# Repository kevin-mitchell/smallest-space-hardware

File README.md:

# smallest-space-hardware
smallest.space hardware related project files

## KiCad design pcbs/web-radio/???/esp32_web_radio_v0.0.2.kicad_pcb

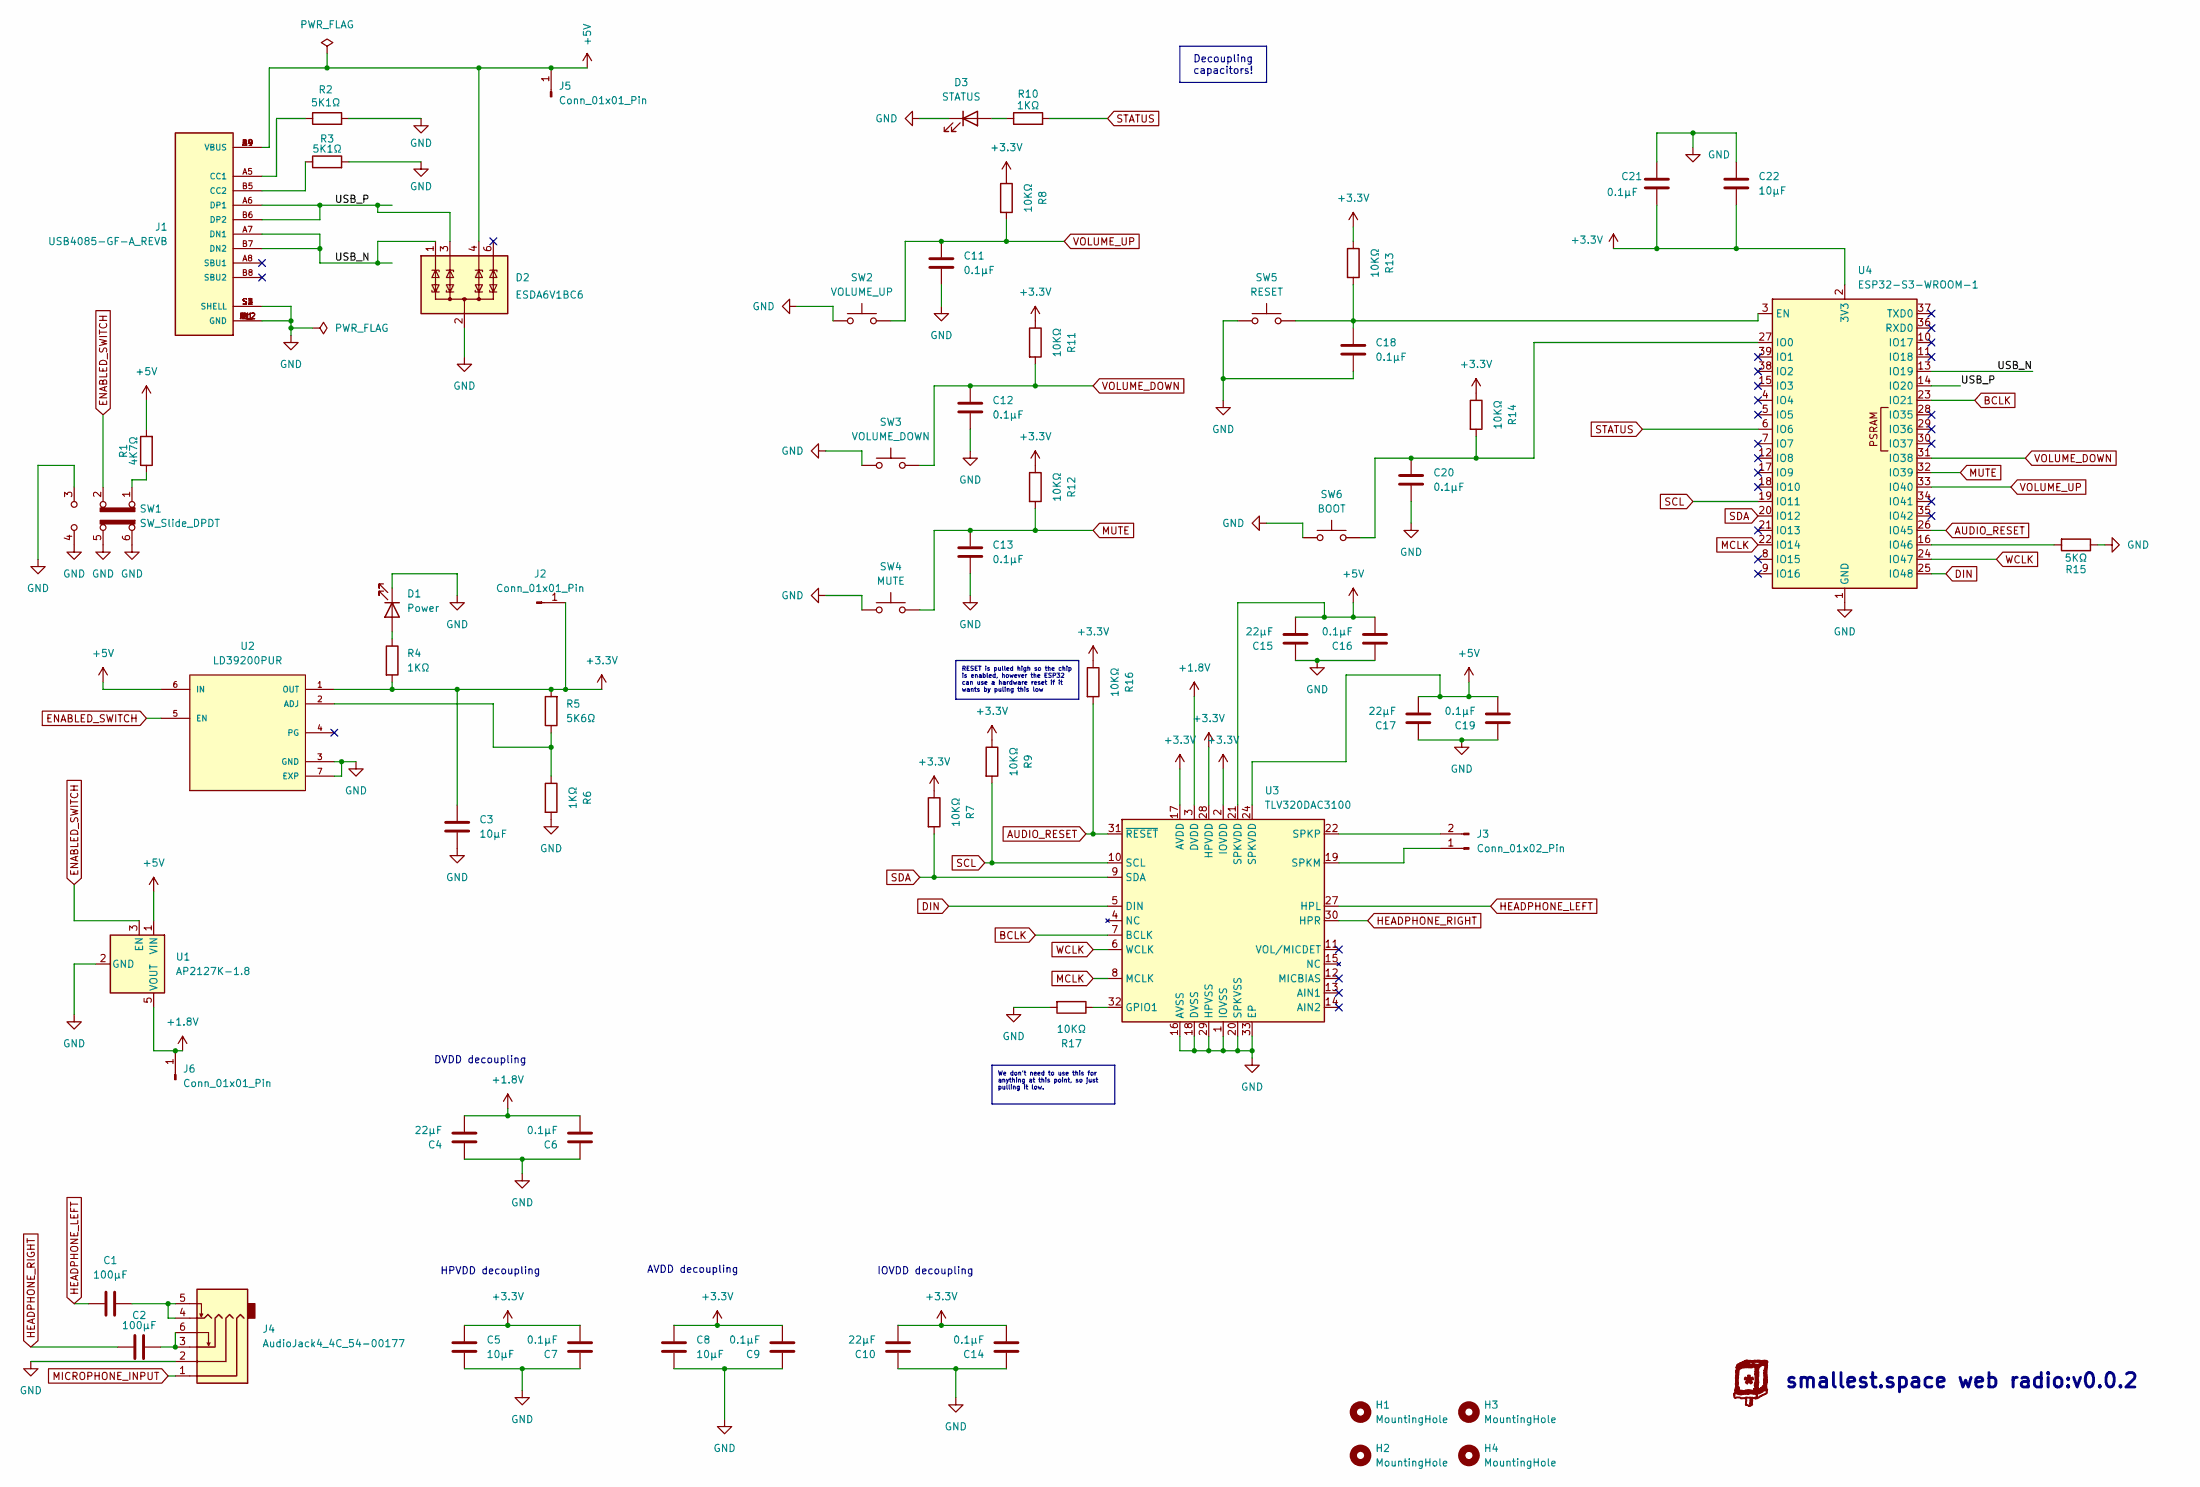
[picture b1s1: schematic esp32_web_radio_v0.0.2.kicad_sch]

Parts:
C1, C2: 100µF; C_1206_3216Metric_Pad1.33x1.80mm_HandSolder
C3, C22: 10µF; C_0805_2012Metric_Pad1.18x1.45mm_HandSolder
C4, C10, C15, C17: 22µF; C_0603_1608Metric_Pad1.08x0.95mm_HandSolder
C5, C8: 10µF; C_0603_1608Metric_Pad1.08x0.95mm_HandSolder
C6, C7, C9, C14, C16, C19: 0.1µF; C_0603_1608Metric_Pad1.08x0.95mm_HandSolder
C11, C12, C13, C18, C20, C21: 0.1µF; C_0805_2012Metric_Pad1.18x1.45mm_HandSolder
D1: Power; LED_0805_2012Metric_Pad1.15x1.40mm_HandSolder
D2: ESDA6V1BC6; SOT-23-6
D3: STATUS; LED_0805_2012Metric_Pad1.15x1.40mm_HandSolder
H1, H2, H3, H4: MountingHole; MountingHole_2.7mm
J1: USB4085-GF-A_REVB; GCT_USB4085-GF-A_REVB; PARTREV B; DigiKey_Part_Number 2073-USB4085-GF-ATR-ND
J2, J5, J6: Conn_01x01_Pin; TestPoint_Pad_1.0x1.0mm
J3: Conn_01x02_Pin; JST_PH_S2B-PH-SM4-TB_1x02-1MP_P2.00mm_Horizontal
J4: AudioJack4_4C_54-00177; 54-00177-headphone-3.5mm-jack
R1: 4K7Ω; R_0805_2012Metric_Pad1.20x1.40mm_HandSolder
R2, R3: 5K1Ω; R_0805_2012Metric_Pad1.20x1.40mm_HandSolder
R4, R6, R10: 1KΩ; R_0805_2012Metric_Pad1.20x1.40mm_HandSolder
R5: 5K6Ω; R_0805_2012Metric_Pad1.20x1.40mm_HandSolder
R7, R8, R9, R11, R12, R13, R14, R16, R17: 10KΩ; R_0805_2012Metric_Pad1.20x1.40mm_HandSolder
R15: 5KΩ; R_0805_2012Metric_Pad1.20x1.40mm_HandSolder
SW1: SW_Slide_DPDT; SLW-913535-2A-SMT
SW2: VOLUME_UP; SW_SPST_PTS810
SW3: VOLUME_DOWN; SW_SPST_PTS810
SW4: MUTE; SW_SPST_PTS810
SW5: RESET; SW_SPST_PTS810
SW6: BOOT; SW_SPST_PTS810
U1: AP2127K-1.8; SOT-23-5
U2: LD39200PUR; SON95P300X300X100-7N; PARTREV 2
U3: TLV320DAC3100; VQFN-32-1EP_5x5mm_P0.5mm_EP3.5x3.5mm
U4: ESP32-S3-WROOM-1

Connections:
+1.8V: C4.2, C6.2, J6.1 (Pin_1_1), U1.5 (VOUT), U3.3 (DVDD)
+3.3V: C3.1, C5.2, C7.2, C8.2, C9.2, C10.2, C14.2, C21.2, C22.2, J2.1 (Pin_1_1), R4.2, R5.2, R7.1, R8.1, R9.1, R11.1, R12.1, R13.1, R14.1, R16.1, U2.1 (OUT), U3.2 (IOVDD), U3.17 (AVDD), U3.28 (HPVDD), U4.2 (3V3)
+5V: C15.2, C16.2, C17.2, C19.2, D2.4 (TVS3), J1.A4 (VBUS), J1.A9 (VBUS), J1.B4 (VBUS), J1.B9 (VBUS), J5.1 (Pin_1_1), R1.2, U1.1 (VIN), U2.6 (IN), U3.21 (SPKVDD), U3.24 (SPKVDD)
/USB_N: D2.1 (TVS1), J1.A7 (DN1), J1.B7 (DN2), U4.13 (IO19)
/USB_P: D2.3 (TVS2), J1.A6 (DP1), J1.B6 (DP2), U4.14 (IO20)
AUDIO_RESET: R16.2, U3.31 (~RESET), U4.26 (IO45)
BCLK: U3.7 (BCLK), U4.23 (IO21)
DIN: U3.5 (DIN), U4.25 (IO48)
ENABLED_SWITCH: SW1.2 (B), U1.3 (EN), U2.5 (EN)
GND: C3.2, C4.1, C5.1, C6.1, C7.1, C8.1, C9.1, C10.1, C11.2, C12.2, C13.2, C14.1, C15.1, C16.1, C17.1, C18.2, C19.1, C20.2, C21.1, C22.1, D1.1 (K), D2.2 (COM), D2.5 (COM), D3.1 (K), J1.A1 (GND), J1.A12 (GND), J1.B1 (GND), J1.B12 (GND), J1.S1 (SHELL), J1.S2 (SHELL), J1.S3 (SHELL), J1.S4 (SHELL), J4.2, R2.2, R3.2, R6.2, R15.1, R17.2, SW1.3 (C), SW1.4 (A), SW1.5 (B), SW1.6 (C), SW2.1, SW3.1, SW4.1, SW5.1, SW6.1, U1.2 (GND), U2.3 (GND), U2.7 (EXP), U3.1 (IOVSS), U3.16 (AVSS), U3.18 (DVSS), U3.20 (SPKVSS), U3.25 (SPKVSS), U3.29 (HPVSS), U3.33 (EP), U4.1 (GND), U4.40 (GND), U4.41 (GND)
HEADPHONE_LEFT: C1.2, U3.27 (HPL)
HEADPHONE_RIGHT: C2.2, U3.30 (HPR)
MCLK: U3.8 (MCLK), U4.22 (IO14)
MICROPHONE_INPUT: J4.1
MUTE: C13.1, R12.2, SW4.2, U4.32 (IO39)
unnamed: C1.1, J4.4, J4.5
unnamed: C2.1, J4.3, J4.6
unnamed: D1.2 (A), R4.1
unnamed: D3.2 (A), R10.1
unnamed: J1.A5 (CC1), R2.1
unnamed: J1.B5 (CC2), R3.1
unnamed: J3.1, U3.19 (SPKM), U3.23 (SPKM)
unnamed: J3.2, U3.22 (SPKP), U3.26 (SPKP)
unnamed: R1.1, SW1.1 (A)
unnamed: R5.1, R6.1, U2.2 (ADJ)
unnamed: R17.1, U3.32 (GPIO1)
unnamed: C18.1, R13.2, SW5.2, U4.3 (EN)
unnamed: C20.1, R14.2, SW6.2, U4.27 (IO0)
unnamed: R15.2, U4.16 (IO46)
SCL: R9.2, U3.10 (SCL), U4.19 (IO11)
SDA: R7.2, U3.9 (SDA), U4.20 (IO12)
STATUS: R10.2, U4.6 (IO6)
VOLUME_DOWN: C12.1, R11.2, SW3.2, U4.31 (IO38)
VOLUME_UP: C11.1, R8.2, SW2.2, U4.33 (IO40)
WCLK: U3.6 (WCLK), U4.24 (IO47)

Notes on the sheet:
DVDD decoupling
HPVDD decoupling
smallest.space web radio:v0.0.2
AVDD decoupling
IOVDD decoupling
RESET is pulled high so the chip is enabled, however the ESP32 can use a hardware reset if it wants by puling this low
We don't need to use this for anything at this point, so just pulling it low.
Decoupling capacitors!

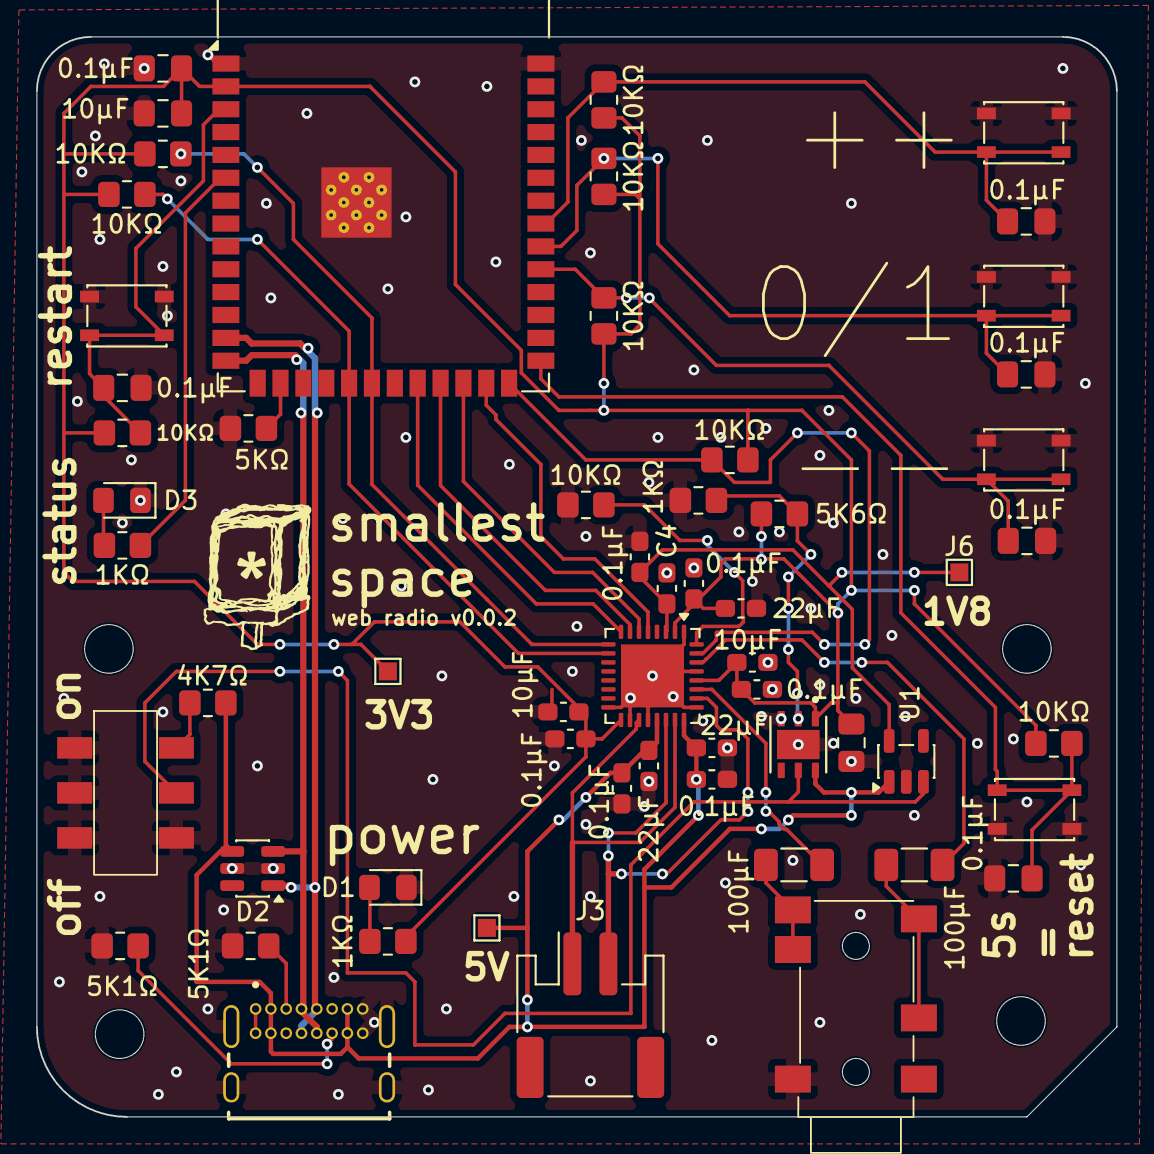
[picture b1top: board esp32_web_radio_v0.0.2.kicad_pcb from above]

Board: 4 copper layers, 60.0 x 60.0 mm, 62 parts (0 on the bottom side), 34 nets.

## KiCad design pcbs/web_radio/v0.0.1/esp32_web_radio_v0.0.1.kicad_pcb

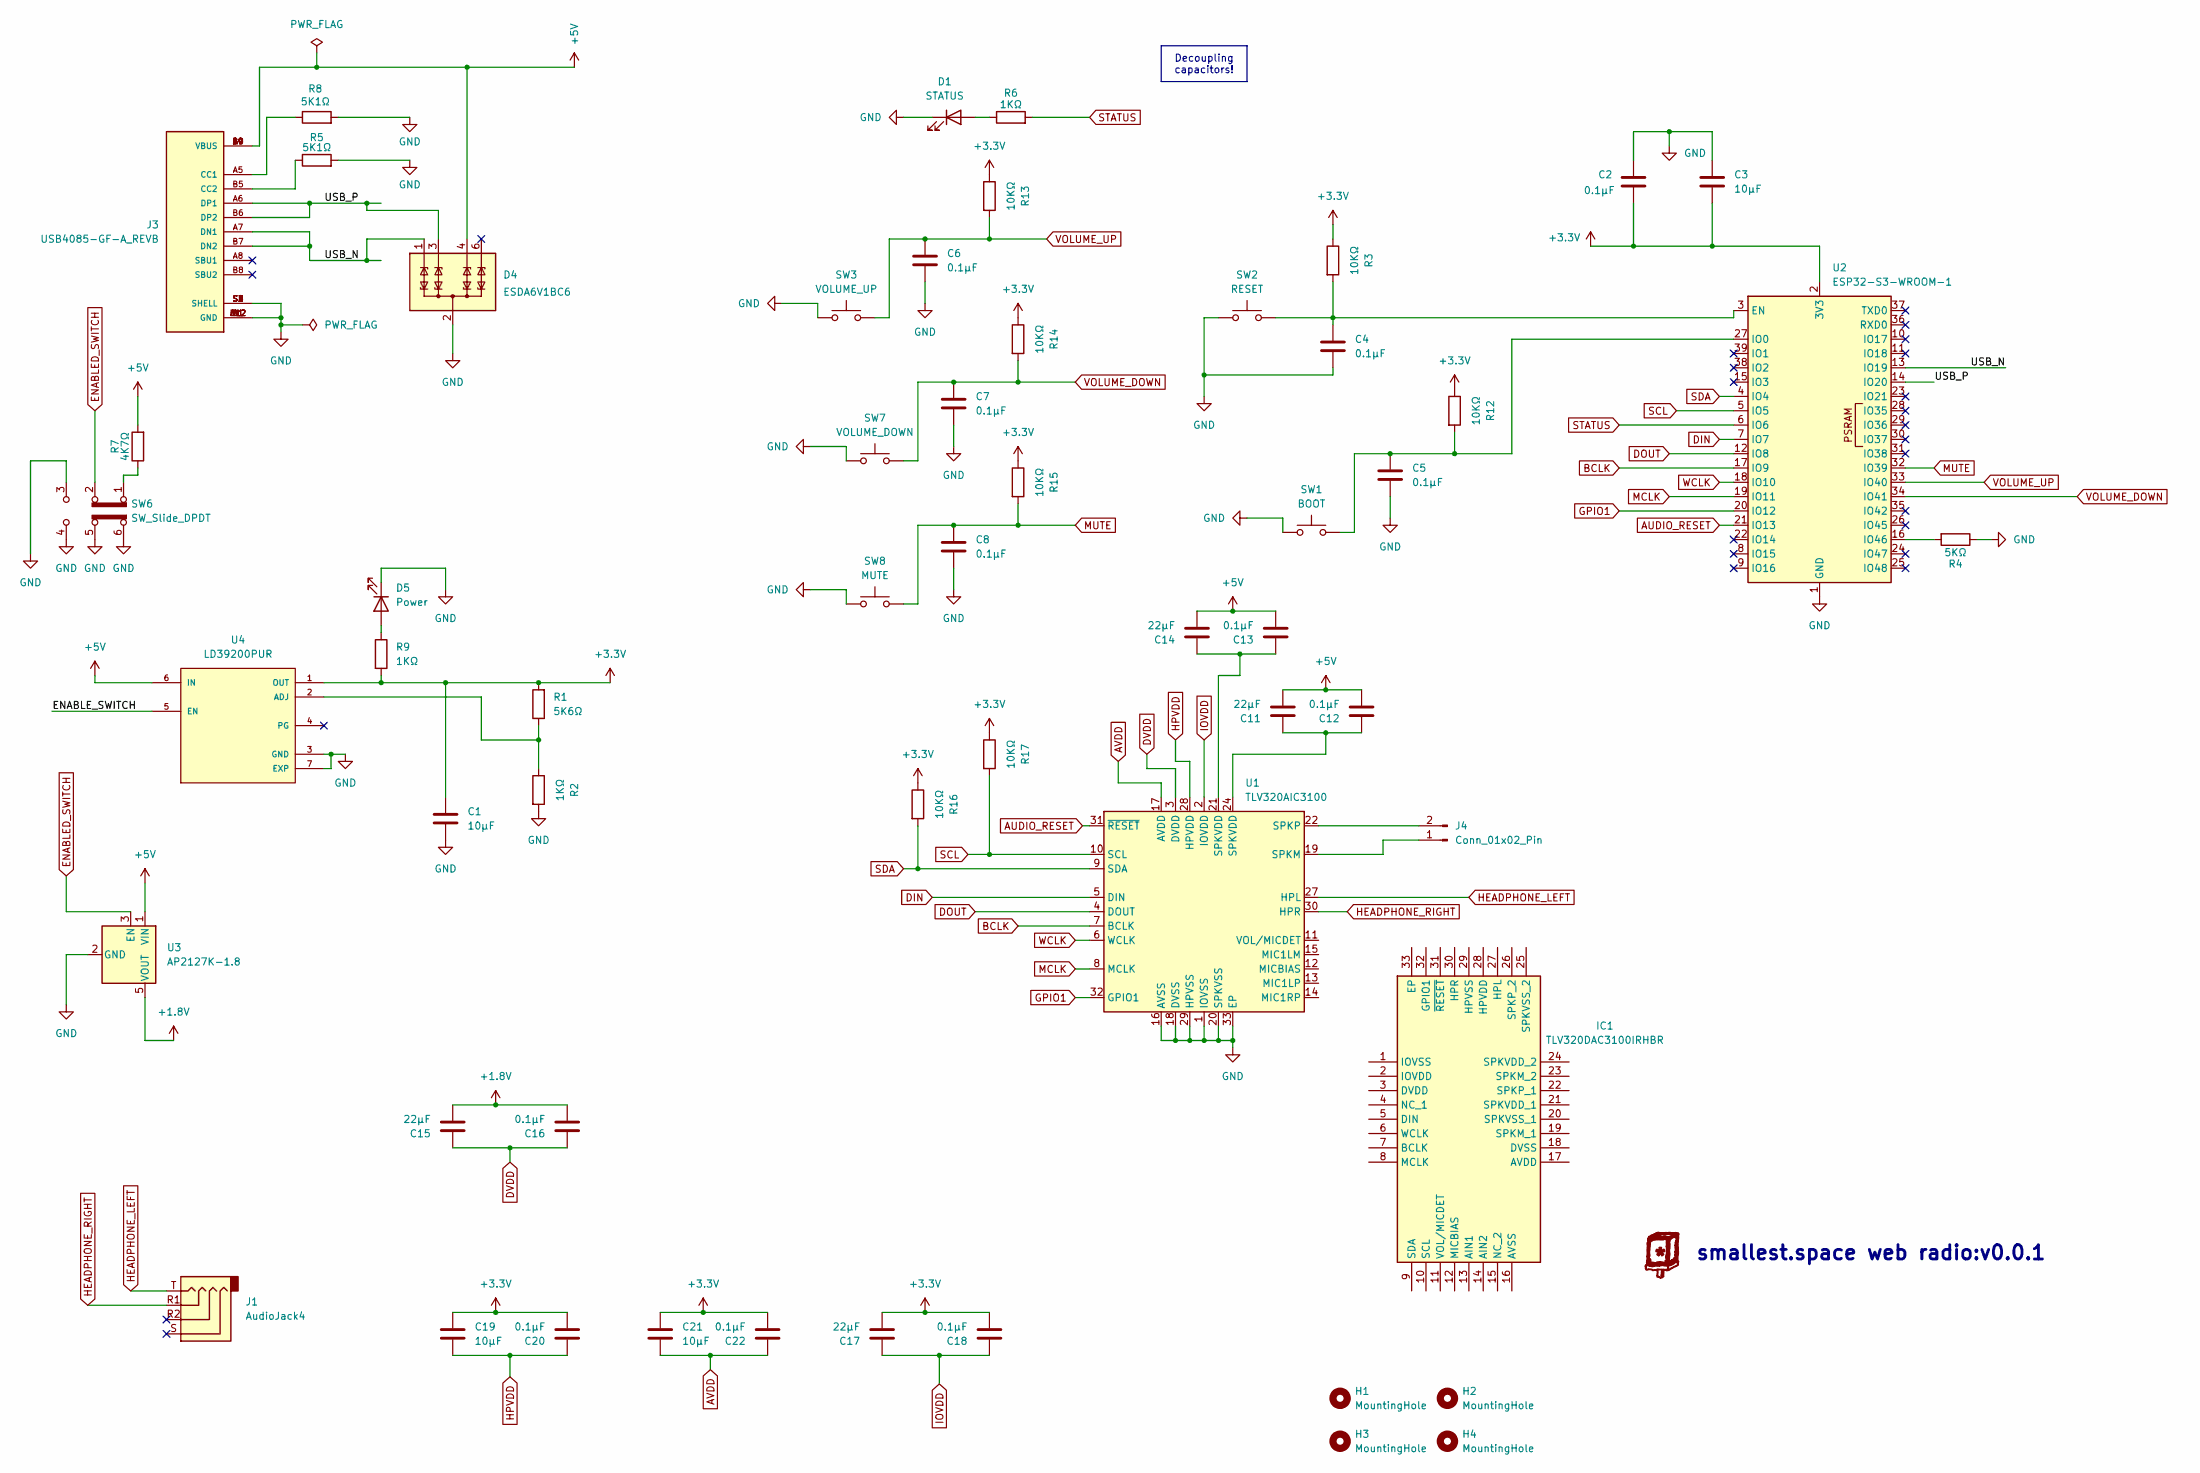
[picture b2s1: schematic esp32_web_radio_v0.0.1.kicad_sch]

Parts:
C1, C3, C19, C21: 10µF; C_0805_2012Metric_Pad1.18x1.45mm_HandSolder
C2, C4, C5, C6, C7, C8, C12, C13, C16, C18, C20, C22: 0.1µF; C_0805_2012Metric_Pad1.18x1.45mm_HandSolder
C11, C14, C15, C17: 22µF; C_0805_2012Metric_Pad1.18x1.45mm_HandSolder
D1: STATUS; LED_0805_2012Metric_Pad1.15x1.40mm_HandSolder
D4: ESDA6V1BC6; SOT-23-6
D5: Power; LED_0805_2012Metric_Pad1.15x1.40mm_HandSolder
H1, H2, H3, H4: MountingHole; MountingHole_2.5mm
IC1: TLV320DAC3100IRHBR; QFN50P500X500X100-33N-D; Manufacturer_Part_Number TLV320DAC3100IRHBR; Mouser Part Number 595-V320DAC3100IRHBR
J1: AudioJack4
J3: USB4085-GF-A_REVB; GCT_USB4085-GF-A_REVB; PARTREV B; DigiKey_Part_Number 2073-USB4085-GF-ATR-ND
J4: Conn_01x02_Pin; JST_PH_S2B-PH-SM4-TB_1x02-1MP_P2.00mm_Horizontal
R1: 5K6Ω; R_0805_2012Metric_Pad1.20x1.40mm_HandSolder
R2, R6, R9: 1KΩ; R_0805_2012Metric_Pad1.20x1.40mm_HandSolder
R3, R12, R13, R14, R15, R16, R17: 10KΩ; R_0805_2012Metric_Pad1.20x1.40mm_HandSolder
R4: 5KΩ; R_0805_2012Metric_Pad1.20x1.40mm_HandSolder
R5, R8: 5K1Ω; R_0805_2012Metric_Pad1.20x1.40mm_HandSolder
R7: 4K7Ω; R_0805_2012Metric_Pad1.20x1.40mm_HandSolder
SW1: BOOT; SW_SPST_PTS810
SW2: RESET; SW_SPST_PTS810
SW3: VOLUME_UP; SW_SPST_PTS810
SW6: SW_Slide_DPDT
SW7: VOLUME_DOWN; SW_SPST_PTS810
SW8: MUTE; SW_SPST_PTS810
U1: TLV320AIC3100; VQFN-32-1EP_5x5mm_P0.5mm_EP3.5x3.5mm
U2: ESP32-S3-WROOM-1
U3: AP2127K-1.8; SOT-23-5
U4: LD39200PUR; SON95P300X300X100-7N; PARTREV 2

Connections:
+1.8V: C15.2, C16.2, U3.5 (VOUT)
+3.3V: C1.1, C2.2, C3.2, C17.2, C18.2, C19.2, C20.2, C21.2, C22.2, R1.2, R3.1, R9.2, R12.1, R13.1, R14.1, R15.1, R16.1, R17.1, U2.2 (3V3), U4.1 (OUT); also elsewhere on the board
/ENABLE_SWITCH: U4.5 (EN)
/USB_N: D4.1 (TVS1), J3.A7 (DN1), J3.B7 (DN2), U2.13 (IO19)
/USB_P: D4.3 (TVS2), J3.A6 (DP1), J3.B6 (DP2), U2.14 (IO20)
AUDIO_RESET: U1.31 (~RESET), U2.21 (IO13)
AVDD: C21.1, C22.1, U1.17 (AVDD)
BCLK: U1.7 (BCLK), U2.17 (IO9)
DIN: U1.5 (DIN), U2.7 (IO7)
DOUT: U1.4 (DOUT), U2.12 (IO8)
DVDD: C15.1, C16.1, U1.3 (DVDD)
ENABLED_SWITCH: SW6.2 (B), U3.3 (EN)
GND: C1.2, C2.1, C3.1, C4.2, C5.2, C6.2, C7.2, C8.2, D1.1 (K), D4.2 (COM), D4.5 (COM), D5.1 (K), J3.A1 (GND), J3.A12 (GND), J3.B1 (GND), J3.B12 (GND), J3.S1 (SHELL), J3.S2 (SHELL), J3.S3 (SHELL), J3.S4 (SHELL), R2.2, R4.1, R5.2, R8.2, SW1.1, SW2.1, SW3.1, SW6.3 (C), SW6.4 (A), SW6.5 (B), SW6.6 (C), SW7.1, SW8.1, U1.1 (IOVSS), U1.16 (AVSS), U1.18 (DVSS), U1.20 (SPKVSS), U1.25 (SPKVSS), U1.29 (HPVSS), U1.33 (EP), U2.1 (GND), U2.40 (GND), U2.41 (GND), U3.2 (GND), U4.3 (GND), U4.7 (EXP); also elsewhere on the board
GPIO1: U1.32 (GPIO1), U2.20 (IO12)
HEADPHONE_LEFT: J1.T, U1.27 (HPL)
HEADPHONE_RIGHT: J1.R1, U1.30 (HPR)
HPVDD: C19.1, C20.1, U1.28 (HPVDD)
IOVDD: C17.1, C18.1, U1.2 (IOVDD)
MCLK: U1.8 (MCLK), U2.19 (IO11)
MUTE: C8.1, R15.2, SW8.2, U2.32 (IO39)
unnamed: C11.1, C12.1, U1.24 (SPKVDD)
unnamed: C13.1, C14.1, U1.21 (SPKVDD)
unnamed: D1.2 (A), R6.1
unnamed 28: R7.1, SW6.1 (A); also elsewhere on the board
unnamed: D5.2 (A), R9.1
unnamed: J3.A5 (CC1), R8.1
unnamed: J3.B5 (CC2), R5.1
unnamed: J4.1, U1.19 (SPKM), U1.23 (SPKM)
unnamed: J4.2, U1.22 (SPKP), U1.26 (SPKP)
unnamed: C4.1, R3.2, SW2.2, U2.3 (EN)
unnamed: C5.1, R12.2, SW1.2, U2.27 (IO0)
unnamed: R4.2, U2.16 (IO46)
unnamed: R1.1, R2.1, U4.2 (ADJ)
SCL: R17.2, U1.10 (SCL), U2.5 (IO5)
SDA: R16.2, U1.9 (SDA), U2.4 (IO4)
STATUS: R6.2, U2.6 (IO6)
VOLUME_DOWN: C7.1, R14.2, SW7.2, U2.34 (IO41)
VOLUME_UP: C6.1, R13.2, SW3.2, U2.33 (IO40)
WCLK: U1.6 (WCLK), U2.18 (IO10)

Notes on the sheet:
smallest.space web radio:v0.0.1
Decoupling capacitors!

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
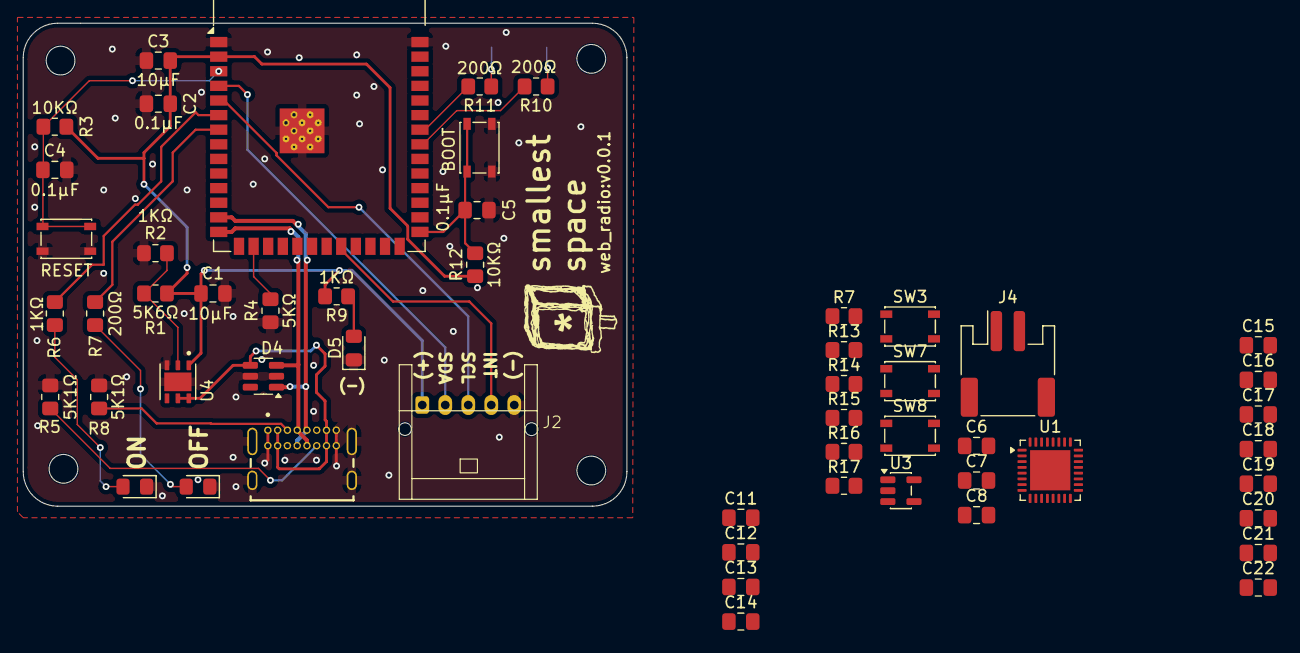
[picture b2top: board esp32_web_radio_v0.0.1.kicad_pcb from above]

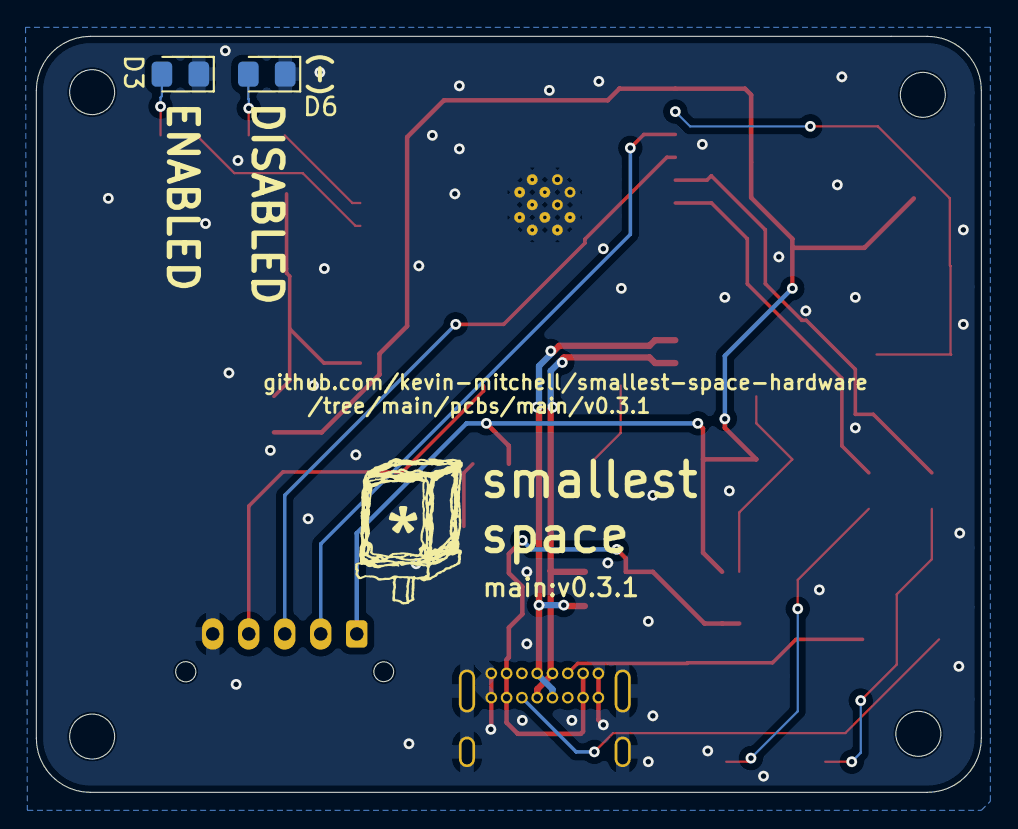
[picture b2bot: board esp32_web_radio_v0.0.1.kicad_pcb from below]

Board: 4 copper layers, 52.5 x 42.0 mm, 60 parts (2 on the bottom side), 38 nets.

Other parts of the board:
D2, D6: DISABLED; LED_0805_2012Metric_Pad1.15x1.40mm_HandSolder
D3: ENABLED; LED_0805_2012Metric_Pad1.15x1.40mm_HandSolder
J2: Conn_01x05_Pin; JST_S05B-PASK-2_1x05_P2.00mm_Side_entry
R7#2: 4K7Ω; R_0805_2012Metric_Pad1.20x1.40mm_HandSolder
R10, R11: 200Ω; R_0805_2012Metric_Pad1.20x1.40mm_HandSolder

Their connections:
+3.3V: J2.1; also elsewhere on the board
GND: D2.1 (K), D3.1 (K), D6.1 (K), J2.5; also elsewhere on the board
unnamed 28: D2.2 (A); also elsewhere on the board
unnamed: D3.2 (A), R10.1
unnamed: D6.2 (A), R11.1

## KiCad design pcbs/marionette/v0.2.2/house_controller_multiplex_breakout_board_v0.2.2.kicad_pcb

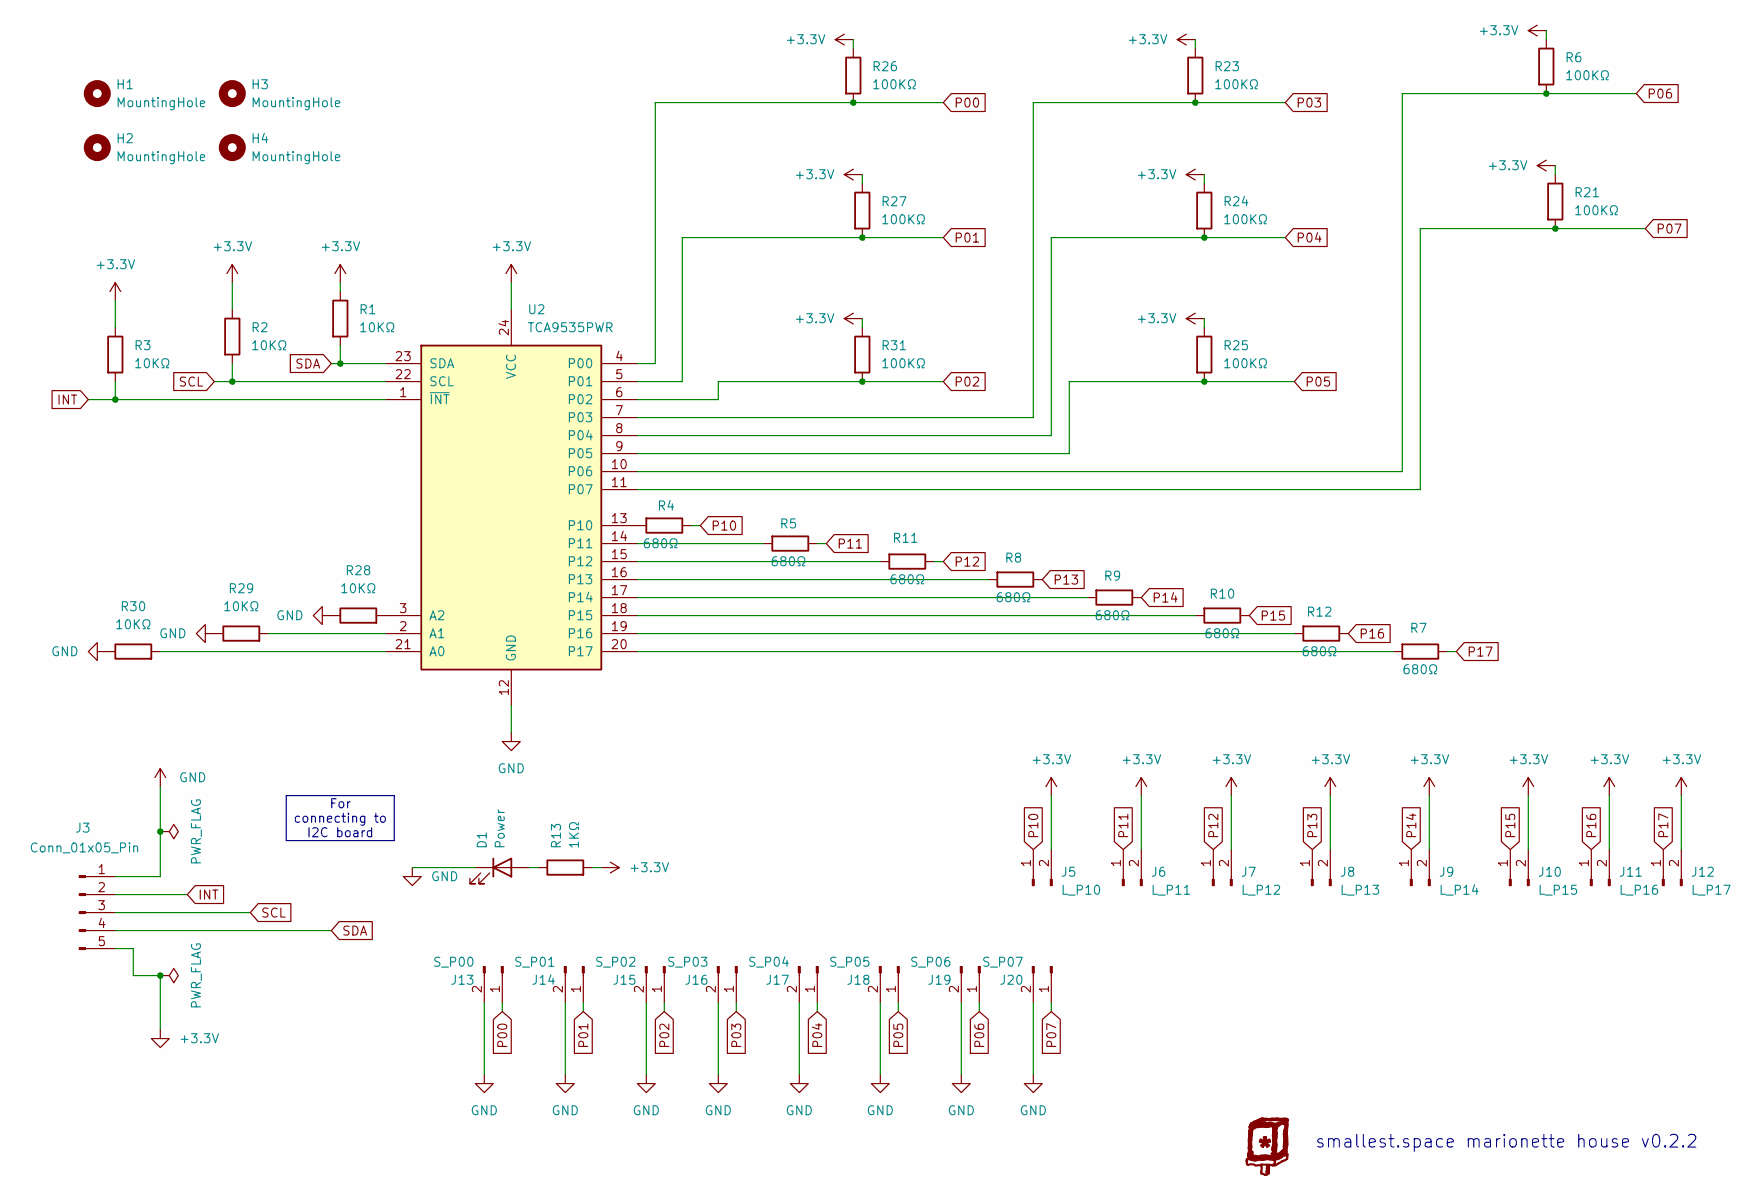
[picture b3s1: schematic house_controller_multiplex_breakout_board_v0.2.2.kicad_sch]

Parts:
D1: Power; LED_0805_2012Metric_Pad1.15x1.40mm_HandSolder
H1, H2, H3, H4: MountingHole; MountingHole_2.5mm
J3: Conn_01x05_Pin; JST_S05B-PASK-2_1x05_P2.00mm_Side_entry
J5: L_P10; JST_S02B-PASK-2_1x02_P2.00mm_Side_entry
J6: L_P11; JST_S02B-PASK-2_1x02_P2.00mm_Side_entry
J7: L_P12; JST_S02B-PASK-2_1x02_P2.00mm_Side_entry
J8: L_P13; JST_S02B-PASK-2_1x02_P2.00mm_Side_entry
J9: L_P14; JST_S02B-PASK-2_1x02_P2.00mm_Side_entry
J10: L_P15; JST_S02B-PASK-2_1x02_P2.00mm_Side_entry
J11: L_P16; JST_S02B-PASK-2_1x02_P2.00mm_Side_entry
J12: L_P17; JST_S02B-PASK-2_1x02_P2.00mm_Side_entry
J13: S_P00; JST_S02B-PASK-2_1x02_P2.00mm_Side_entry
J14: S_P01; JST_S02B-PASK-2_1x02_P2.00mm_Side_entry
J15: S_P02; JST_S02B-PASK-2_1x02_P2.00mm_Side_entry
J16: S_P03; JST_S02B-PASK-2_1x02_P2.00mm_Side_entry
J17: S_P04; JST_S02B-PASK-2_1x02_P2.00mm_Side_entry
J18: S_P05; JST_S02B-PASK-2_1x02_P2.00mm_Side_entry
J19: S_P06; JST_S02B-PASK-2_1x02_P2.00mm_Side_entry
J20: S_P07; JST_S02B-PASK-2_1x02_P2.00mm_Side_entry
R1, R2, R3, R28, R29, R30: 10KΩ; R_0805_2012Metric_Pad1.20x1.40mm_HandSolder
R4, R5, R7, R8, R9, R10, R11, R12: 680Ω; R_0805_2012Metric_Pad1.20x1.40mm_HandSolder
R6, R21, R23, R24, R25, R26, R27, R31: 100KΩ; R_0805_2012Metric_Pad1.20x1.40mm_HandSolder
R13: 1KΩ; R_0805_2012Metric_Pad1.20x1.40mm_HandSolder
U2: TCA9535PWR; TSSOP-24_4.4x7.8mm_P0.65mm

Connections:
+3.3V: J3.5, J5.2, J6.2, J7.2, J8.2, J9.2, J10.2, J11.2, J12.2, R1.1, R2.1, R3.1, R6.1, R13.2, R21.1, R23.1, R24.1, R25.1, R26.1, R27.1, R31.1, U2.24 (VCC)
GND: D1.1 (K), J3.1, J13.2, J14.2, J15.2, J16.2, J17.2, J18.2, J19.2, J20.2, R28.1, R29.1, R30.1, U2.12 (GND)
INT: J3.2, R3.2, U2.1 (~INT)
unnamed: D1.2 (A), R13.1
unnamed: R30.2, U2.21 (A0)
unnamed: R29.2, U2.2 (A1)
unnamed: R28.2, U2.3 (A2)
unnamed: R4.2, U2.13 (P10)
unnamed: R5.2, U2.14 (P11)
unnamed: R11.2, U2.15 (P12)
unnamed: R8.2, U2.16 (P13)
unnamed: R9.2, U2.17 (P14)
unnamed: R10.2, U2.18 (P15)
unnamed: R12.2, U2.19 (P16)
unnamed: R7.2, U2.20 (P17)
P00: J13.1, R26.2, U2.4 (P00)
P01: J14.1, R27.2, U2.5 (P01)
P02: J15.1, R31.2, U2.6 (P02)
P03: J16.1, R23.2, U2.7 (P03)
P04: J17.1, R24.2, U2.8 (P04)
P05: J18.1, R25.2, U2.9 (P05)
P06: J19.1, R6.2, U2.10 (P06)
P07: J20.1, R21.2, U2.11 (P07)
P10: J5.1, R4.1
P11: J6.1, R5.1
P12: J7.1, R11.1
P13: J8.1, R8.1
P14: J9.1, R9.1
P15: J10.1, R10.1
P16: J11.1, R12.1
P17: J12.1, R7.1
SCL: J3.3, R2.2, U2.22 (SCL)
SDA: J3.4, R1.2, U2.23 (SDA)

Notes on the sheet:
smallest.space marionette house v0.2.2
For connecting to I2C board

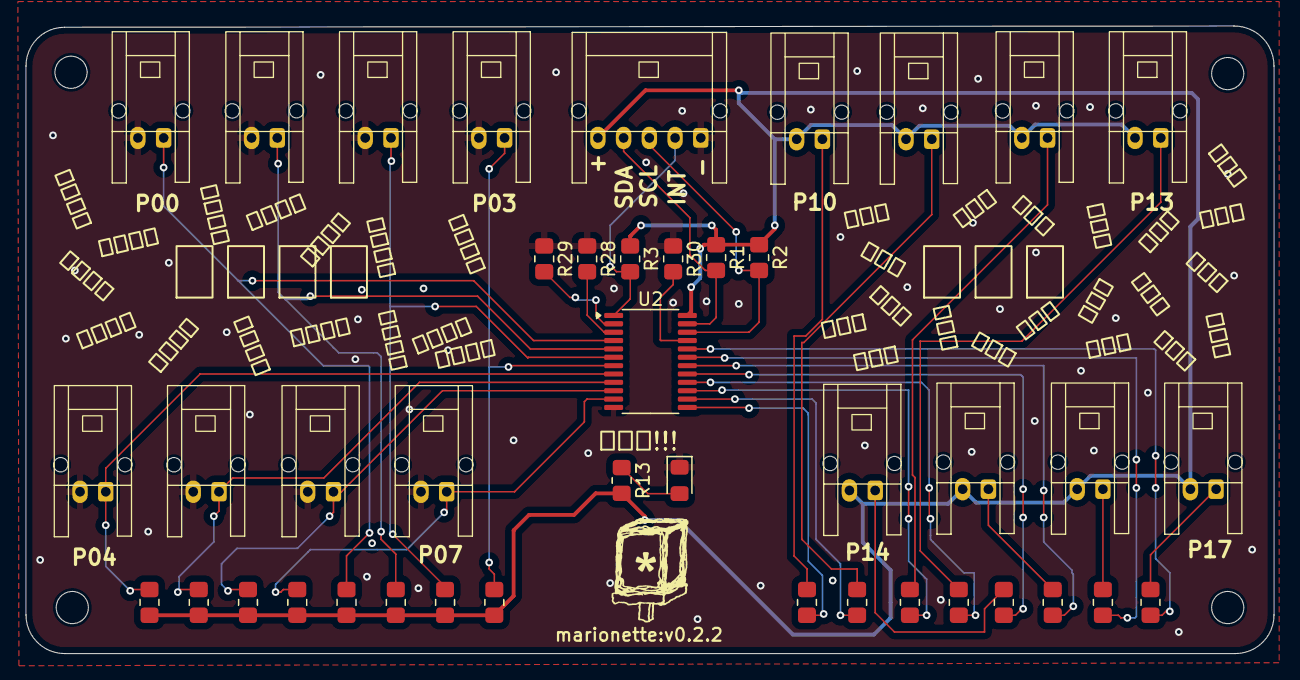
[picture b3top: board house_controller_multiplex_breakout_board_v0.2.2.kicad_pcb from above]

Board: 4 copper layers, 97.0 x 48.8 mm, 46 parts (0 on the bottom side), 33 nets.
